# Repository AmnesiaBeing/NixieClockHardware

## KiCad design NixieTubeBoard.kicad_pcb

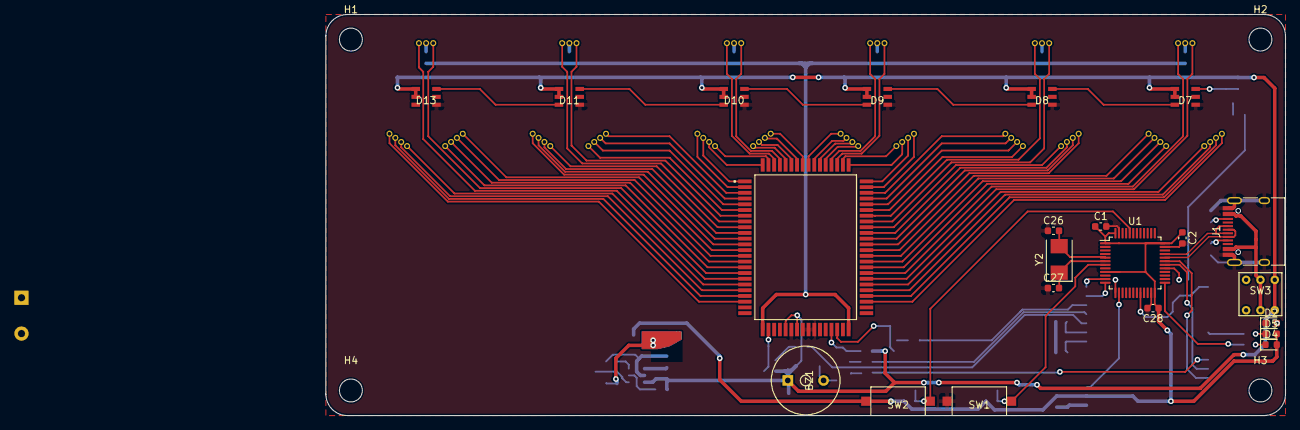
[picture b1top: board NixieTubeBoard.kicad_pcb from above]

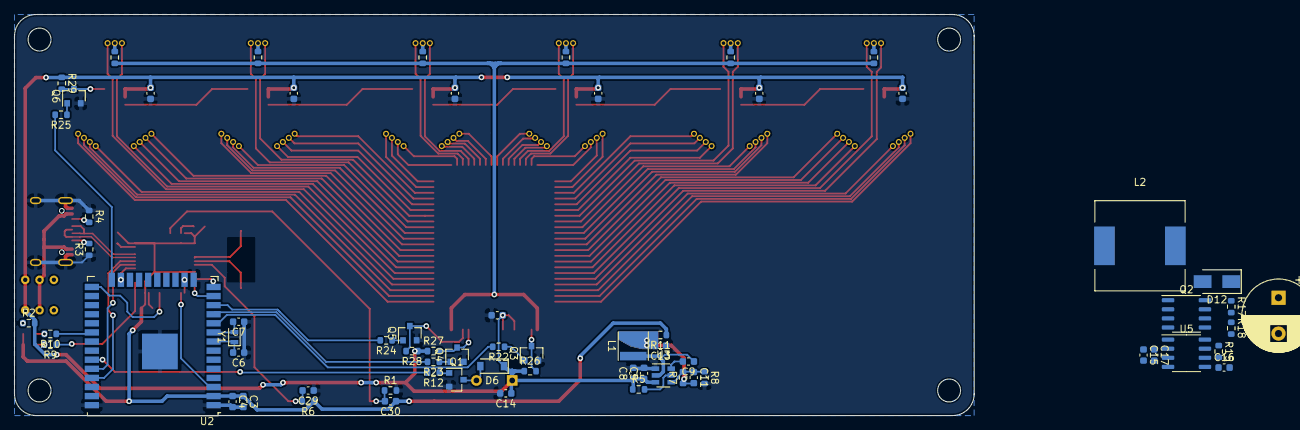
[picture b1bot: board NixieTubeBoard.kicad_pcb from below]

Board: 2 copper layers, 134.0 x 56.0 mm, 98 parts (66 on the bottom side), 124 nets.

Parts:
BZ1: Buzzer_C200213
C1, C3, C28: 100uF; C_0603_1608Metric
C2, C4, C8, C9, C16, C25: 100nF; C_0603_1608Metric
C5, C13: 22uF; C_0603_1608Metric
C6, C7, C14, C19, C20, C21, C22, C23, C26, C27, C29, C30: C; C_0603_1608Metric
C11: NC; C_0603_1608Metric
C15: 470uF; C_0603_1608Metric
C17: 330uF; C_0603_1608Metric
C18: 10uF/250V; CP_Radial_D10.0mm_P5.00mm
C24: 100nF×6; C_0603_1608Metric
D2: RED; LED_0603_1608Metric
D4: GREEN; LED_0603_1608Metric
D5: BLUE; LED_0603_1608Metric
D6: 1N4148; D_SOD-123
D7, D8, D9, D10, D11, D13: TC3838
D12: ES1J; D_SMA
H1, H2, H3, H4: MountingHole; MountingHole_3.2mm_M3
J1: USB_C_Receptacle_USB2.0; USB_C_Receptacle_HRO_TYPE-C-31-M-12
L1: 2.2uH; L_Taiyo-Yuden_MD-4040
L2: 220uH; L_12x12mm_H4.5mm
N1, N2, N3, N4, N5: NixieTube; NixieTubeJack
N6: NixieTube×6; NixieTubeJack
Q1, Q3, Q4, Q5, Q6: S8050_BEC; SOT-23
Q2: FDS2672CT; SO-8_3.9x4.9mm_P1.27mm
R1, R6, R8, R26, R27, R28, R29: 10KΩ; R_0603_1608Metric
R2, R9, R10: 1KΩ; R_0603_1608Metric
R3, R4: 5.1KΩ; R_0603_1608Metric
R5: 100KΩ; R_0603_1608Metric
R7: 30KΩ; R_0603_1608Metric
R11: 0; R_0603_1608Metric
R12, R22, R23, R24, R25: R; R_0603_1608Metric
R13, R14, R16, R19, R20, R21: 33KΩ; R_0603_1608Metric
R15: 50mΩ; R_0603_1608Metric
R17: 1.8MΩ; R_0603_1608Metric
R18: 16KΩ; R_0603_1608Metric
SW1, SW2: SW_Push; BUTTON_C2681479
SW3: SW_DPDT_x2; BUTTON_C2681587
U1: STM32L433CBTx; LQFP-48_7x7mm_P0.5mm
U2: ESP32-WROOM-32U
U3: TPS564201; SOT-23-6
U5: MAX1771ESA; SO-8_3.9x4.9mm_P1.27mm
U6: HV507PG-G; QFP80P2390X1790X340-80N
Y1: 32.738kHz; Crystal_SMD_2012-2Pin_2.0x1.2mm
Y2: 32.738kHz; Crystal_SMD_5032-2Pin_5.0x3.2mm

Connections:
+3V3: C1.1, C2.1, C3.1, C4.1, C28.1, C30.1, D4.2, D5.2, R6.1, R11.1, SW2.1, U1.1, U1.9, U1.24, U1.36, U1.48, U2.2
+5V: BZ1.1, C5.1, C8.1, C14.1, C15.1, C17.1, C19.1, C20.1, C21.1, C22.1, C23.1, C24.1, C25.2, D6.1, D7.4, D7.5, D8.4, D8.5, D9.4, D9.5, D10.4, D10.5, D11.4, D11.5, D13.4, D13.5, L2.1, R2.2, R5.1, R26.1, R27.1, R28.1, R29.1, SW3.3, SW3.6, U3.3, U5.2, U6.29, U6.31
/32K_XN: C7.2, U2.9, Y1.2
/32K_XP: C6.2, U2.8, Y1.1
/BUZZER: R12.2, U2.33
/DOWNLOADING: R9.1, U1.25
/ESP32_EN: U1.14, U2.3
/ESP32_IO0: U1.20, U2.25
/ESP32_IO2: R25.2, U2.24
/ESP32_IO12: U1.11, U2.14
/ESP32_IO13: U1.13, U2.16
/ESP32_IO14: U1.12, U2.13
/ESP32_IO15: U1.29, U2.23
/ESP32_IO18: R10.1, U2.30
/ESP32_IO25: R22.2, U2.10
/ESP32_IO26: R23.2, U2.11
/ESP32_IO27: R24.2, U2.12
/ESP32_RXD0: U1.30, U2.34
/ESP32_TXD0: U1.31, U2.35
/HV_CLK_5V: Q4.3, R27.2, U6.37
/HV_DIN_5V: Q3.3, R26.2, U6.26
/HV_LE_5V: Q5.3, R28.2, U6.38
/N10: N1.12, U6.17
/N11: N1.3, U6.18
/N12: N1.4, U6.22
/N13: N1.5, U6.21
/N14: N1.6, U6.20
/N15: N1.7, U6.19
/N16: N1.8, U6.16
/N17: N1.9, U6.15
/N18: N1.10, U6.14
/N19: N1.11, U6.13
/N20: N2.12, U6.7
/N21: N2.3, U6.8
/N22: N2.4, U6.12
/N23: N2.5, U6.11
/N24: N2.6, U6.10
/N25: N2.7, U6.9
/N26: N2.8, U6.6
/N27: N2.9, U6.5
/N28: N2.10, U6.4
/N29: N2.11, U6.3
/N30: N3.12, U6.77
/N31: N3.3, U6.78
/N32: N3.4, U6.2
/N33: N3.5, U6.1
/N34: N3.6, U6.80
/N35: N3.7, U6.79
/N36: N3.8, U6.76
/N37: N3.9, U6.75
/N38: N3.10, U6.74
/N39: N3.11, U6.73
/N40: N4.12, U6.67
/N41: N4.3, U6.68
/N42: N4.4, U6.72
/N43: N4.5, U6.71
/N44: N4.6, U6.70
/N45: N4.7, U6.69
/N46: N4.8, U6.66
/N47: N4.9, U6.65
/N48: N4.10, U6.64
/N49: N4.11, U6.63
/N50: N5.12, U6.57
/N51: N5.3, U6.58
/N52: N5.4, U6.62
/N53: N5.5, U6.61
/N54: N5.6, U6.60
/N55: N5.7, U6.59
/N56: N5.8, U6.56
/N57: N5.9, U6.55
/N58: N5.10, U6.54
/N59: N5.11, U6.53
/N60: N6.12, U6.47
/N61: N6.3, U6.48
/N62: N6.4, U6.52
/N63: N6.5, U6.51
/N64: N6.6, U6.50
/N65: N6.7, U6.49
/N66: N6.8, U6.46
/N67: N6.9, U6.45
/N68: N6.10, U6.44
/N69: N6.11, U6.43
/RGBLED_5V: D7.3, Q6.3, R29.2
/STM32_BOOT0: C30.2, R1.1, SW2.2, U1.44
/STM32_RST: C29.2, R6.2, SW1.2, U1.7
/USB_D+: J1.A6, J1.B6, U1.33
/USB_D-: J1.A7, J1.B7, U1.32
GND: C1.2, C2.2, C3.2, C4.2, C5.2, C6.1, C7.1, C8.2, C13.1, C14.2, C15.2, C16.2, C17.2, C18.2, C19.2, C20.2, C21.2, C22.2, C23.2, C24.2, C25.1, C26.1, C27.1, C28.2, C29.1, D2.1, D7.1, D8.1, D9.1, D10.1, D11.1, D13.1, J1.A1, J1.A12, J1.B1, J1.B12, J1.S1, Q1.2, Q3.2, Q4.2, Q5.2, Q6.2, R1.2, R3.1, R4.1, R8.2, R15.2, R18.2, SW1.1, U1.8, U1.23, U1.35, U1.47, U2.1, U2.15, U2.38, U2.39, U3.1, U5.6, U5.7, U6.30, U6.32, U6.33, U6.34
unnamed: BZ1.2, D6.2, Q1.3
unnamed: C9.1, L1.1, U3.2
unnamed: C9.2, U3.6
unnamed: C11.1, R7.2, R8.1, U3.4
unnamed: C11.2, C13.2, L1.2, R7.1, R11.2
unnamed: C16.1, U5.5
unnamed: C26.2, U1.5, Y2.2
unnamed: C27.2, U1.6, Y2.1
unnamed: D2.2, R2.1
unnamed: D4.1, R9.2
unnamed: D5.1, R10.2
unnamed: D7.6, D8.3
unnamed: D8.6, D9.3
unnamed: D9.6, D10.3
unnamed: D10.6, D11.3
unnamed: D11.6, D13.3
unnamed: D12.2, L2.2, Q2.5, Q2.6, Q2.7, Q2.8
unnamed: J1.A4, J1.A9, J1.B4, J1.B9, SW3.2, SW3.5
unnamed: J1.A5, R3.2
unnamed: J1.B5, R4.2
unnamed: N1.1, R13.2
unnamed: N2.1, R14.2
unnamed: N3.1, R16.2
unnamed: N4.1, R19.2
unnamed: N5.1, R20.2
unnamed: N6.1, R21.2
unnamed: Q1.1, R12.1
unnamed: Q2.1, Q2.2, Q2.3, R15.1, U5.8
unnamed: Q2.4, U5.1
unnamed: Q3.1, R22.1
unnamed: Q4.1, R23.1
unnamed: Q5.1, R24.1
unnamed: Q6.1, R25.1
unnamed: R5.2, U3.5
unnamed: R17.2, R18.1, U5.3
VPP: C18.1, D12.1, R13.1, R14.1, R16.1, R17.1, R19.1, R20.1, R21.1, U6.25, U6.40

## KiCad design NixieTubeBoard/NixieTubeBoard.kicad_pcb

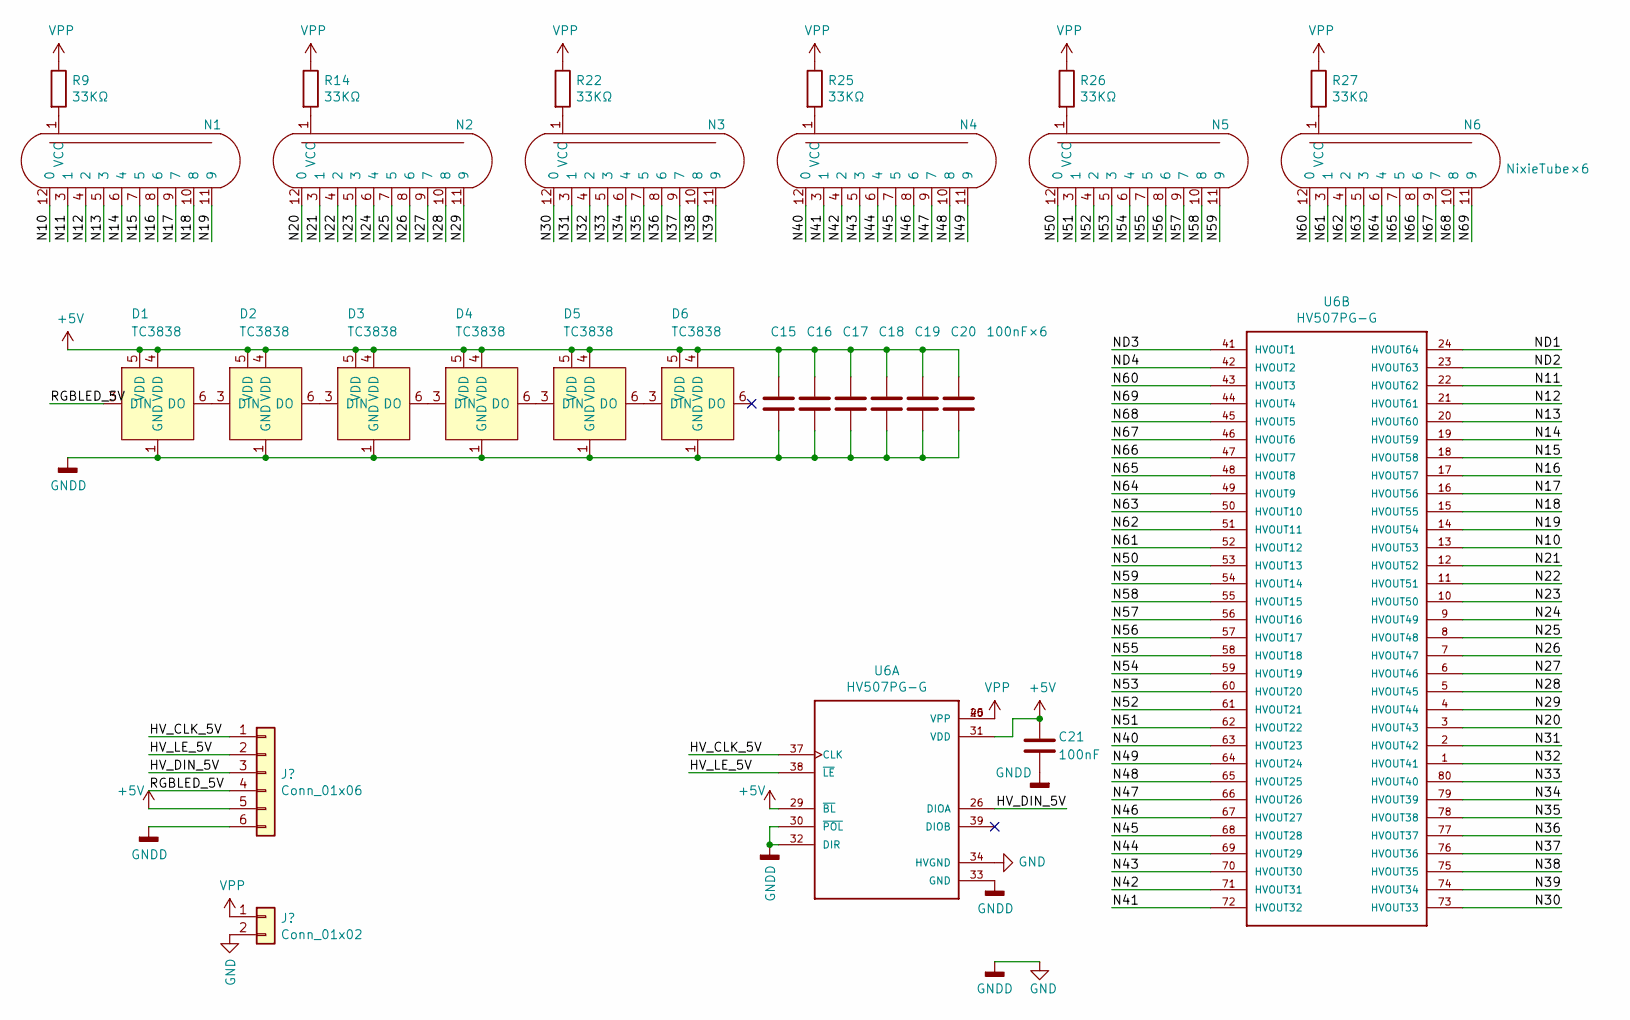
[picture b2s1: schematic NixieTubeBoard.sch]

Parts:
C15, C16, C17, C18, C19: C; C_0603_1608Metric
C20: 100nF×6; C_0603_1608Metric
C21: 100nF; C_0603_1608Metric
D1, D2, D3, D4, D5, D6: TC3838
N1, N2, N3, N4, N5: NixieTube; NixieTubeJack
N6: NixieTube×6; NixieTubeJack
R9, R14, R22, R25, R26, R27: 33KΩ; R_0603_1608Metric
U6: HV507PG-G; QFP80P2390X1790X340-80N

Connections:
+5V: C15.1, C16.1, C17.1, C18.1, C19.1, C20.1, C21.2, D1.4 (VDD), D1.5 (VDD), D2.4 (VDD), D2.5 (VDD), D3.4 (VDD), D3.5 (VDD), D4.4 (VDD), D4.5 (VDD), D5.4 (VDD), D5.5 (VDD), D6.4 (VDD), D6.5 (VDD), U6.29 (~BL~), U6.31 (VDD)
/HV_CLK_5V: U6.37 (CLK)
/HV_DIN_5V: U6.26 (DIOA)
/HV_LE_5V: U6.38 (~LE~)
/N10: N1.12 (0), U6.13 (HVOUT53)
/N11: N1.3 (1), U6.22 (HVOUT62)
/N12: N1.4 (2), U6.21 (HVOUT61)
/N13: N1.5 (3), U6.20 (HVOUT60)
/N14: N1.6 (4), U6.19 (HVOUT59)
/N15: N1.7 (5), U6.18 (HVOUT58)
/N16: N1.8 (6), U6.17 (HVOUT57)
/N17: N1.9 (7), U6.16 (HVOUT56)
/N18: N1.10 (8), U6.15 (HVOUT55)
/N19: N1.11 (9), U6.14 (HVOUT54)
/N20: N2.12 (0), U6.3 (HVOUT43)
/N21: N2.3 (1), U6.12 (HVOUT52)
/N22: N2.4 (2), U6.11 (HVOUT51)
/N23: N2.5 (3), U6.10 (HVOUT50)
/N24: N2.6 (4), U6.9 (HVOUT49)
/N25: N2.7 (5), U6.8 (HVOUT48)
/N26: N2.8 (6), U6.7 (HVOUT47)
/N27: N2.9 (7), U6.6 (HVOUT46)
/N28: N2.10 (8), U6.5 (HVOUT45)
/N29: N2.11 (9), U6.4 (HVOUT44)
/N30: N3.12 (0), U6.73 (HVOUT33)
/N31: N3.3 (1), U6.2 (HVOUT42)
/N32: N3.4 (2), U6.1 (HVOUT41)
/N33: N3.5 (3), U6.80 (HVOUT40)
/N34: N3.6 (4), U6.79 (HVOUT39)
/N35: N3.7 (5), U6.78 (HVOUT38)
/N36: N3.8 (6), U6.77 (HVOUT37)
/N37: N3.9 (7), U6.76 (HVOUT36)
/N38: N3.10 (8), U6.75 (HVOUT35)
/N39: N3.11 (9), U6.74 (HVOUT34)
/N40: N4.12 (0), U6.63 (HVOUT23)
/N41: N4.3 (1), U6.72 (HVOUT32)
/N42: N4.4 (2), U6.71 (HVOUT31)
/N43: N4.5 (3), U6.70 (HVOUT30)
/N44: N4.6 (4), U6.69 (HVOUT29)
/N45: N4.7 (5), U6.68 (HVOUT28)
/N46: N4.8 (6), U6.67 (HVOUT27)
/N47: N4.9 (7), U6.66 (HVOUT26)
/N48: N4.10 (8), U6.65 (HVOUT25)
/N49: N4.11 (9), U6.64 (HVOUT24)
/N50: N5.12 (0), U6.53 (HVOUT13)
/N51: N5.3 (1), U6.62 (HVOUT22)
/N52: N5.4 (2), U6.61 (HVOUT21)
/N53: N5.5 (3), U6.60 (HVOUT20)
/N54: N5.6 (4), U6.59 (HVOUT19)
/N55: N5.7 (5), U6.58 (HVOUT18)
/N56: N5.8 (6), U6.57 (HVOUT17)
/N57: N5.9 (7), U6.56 (HVOUT16)
/N58: N5.10 (8), U6.55 (HVOUT15)
/N59: N5.11 (9), U6.54 (HVOUT14)
/N60: N6.12 (0), U6.43 (HVOUT3)
/N61: N6.3 (1), U6.52 (HVOUT12)
/N62: N6.4 (2), U6.51 (HVOUT11)
/N63: N6.5 (3), U6.50 (HVOUT10)
/N64: N6.6 (4), U6.49 (HVOUT9)
/N65: N6.7 (5), U6.48 (HVOUT8)
/N66: N6.8 (6), U6.47 (HVOUT7)
/N67: N6.9 (7), U6.46 (HVOUT6)
/N68: N6.10 (8), U6.45 (HVOUT5)
/N69: N6.11 (9), U6.44 (HVOUT4)
/RGBLED_5V: D1.3 (DIN)
GND: C15.2, C16.2, C17.2, C18.2, C19.2, C20.2, C21.1, D1.1 (GND), D2.1 (GND), D3.1 (GND), D4.1 (GND), D5.1 (GND), D6.1 (GND), U6.30 (~POL~), U6.32 (DIR), U6.33 (GND), U6.34 (HVGND)
unnamed: D1.6 (DO), D2.3 (DIN)
unnamed: D2.6 (DO), D3.3 (DIN)
unnamed: D3.6 (DO), D4.3 (DIN)
unnamed: D4.6 (DO), D5.3 (DIN)
unnamed: D5.6 (DO), D6.3 (DIN)
unnamed: N1.1 (VCC), R9.2
unnamed: N2.1 (VCC), R14.2
unnamed: N3.1 (VCC), R22.2
unnamed: N4.1 (VCC), R25.2
unnamed: N5.1 (VCC), R26.2
unnamed: N6.1 (VCC), R27.2
VPP: R9.1, R14.1, R22.1, R25.1, R26.1, R27.1, U6.25 (VPP), U6.40 (VPP)

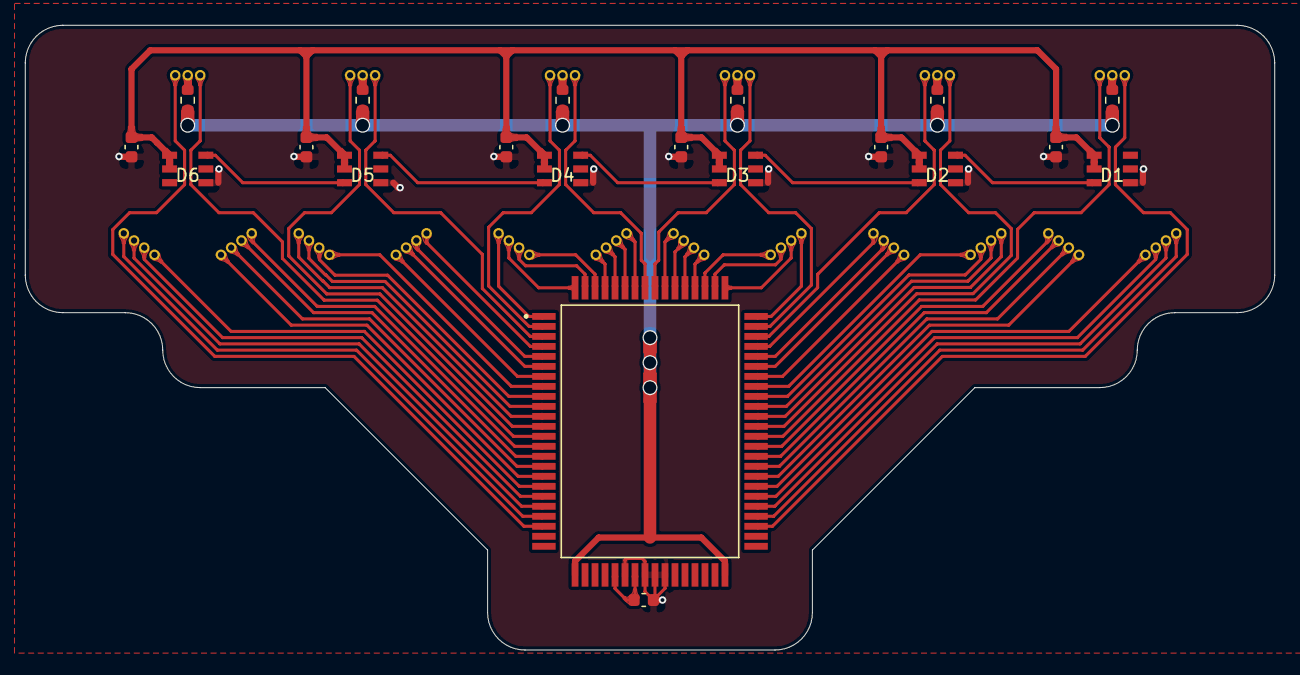
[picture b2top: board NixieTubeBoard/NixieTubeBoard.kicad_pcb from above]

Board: 2 copper layers, 100.0 x 50.0 mm, 26 parts (0 on the bottom side), 74 nets.

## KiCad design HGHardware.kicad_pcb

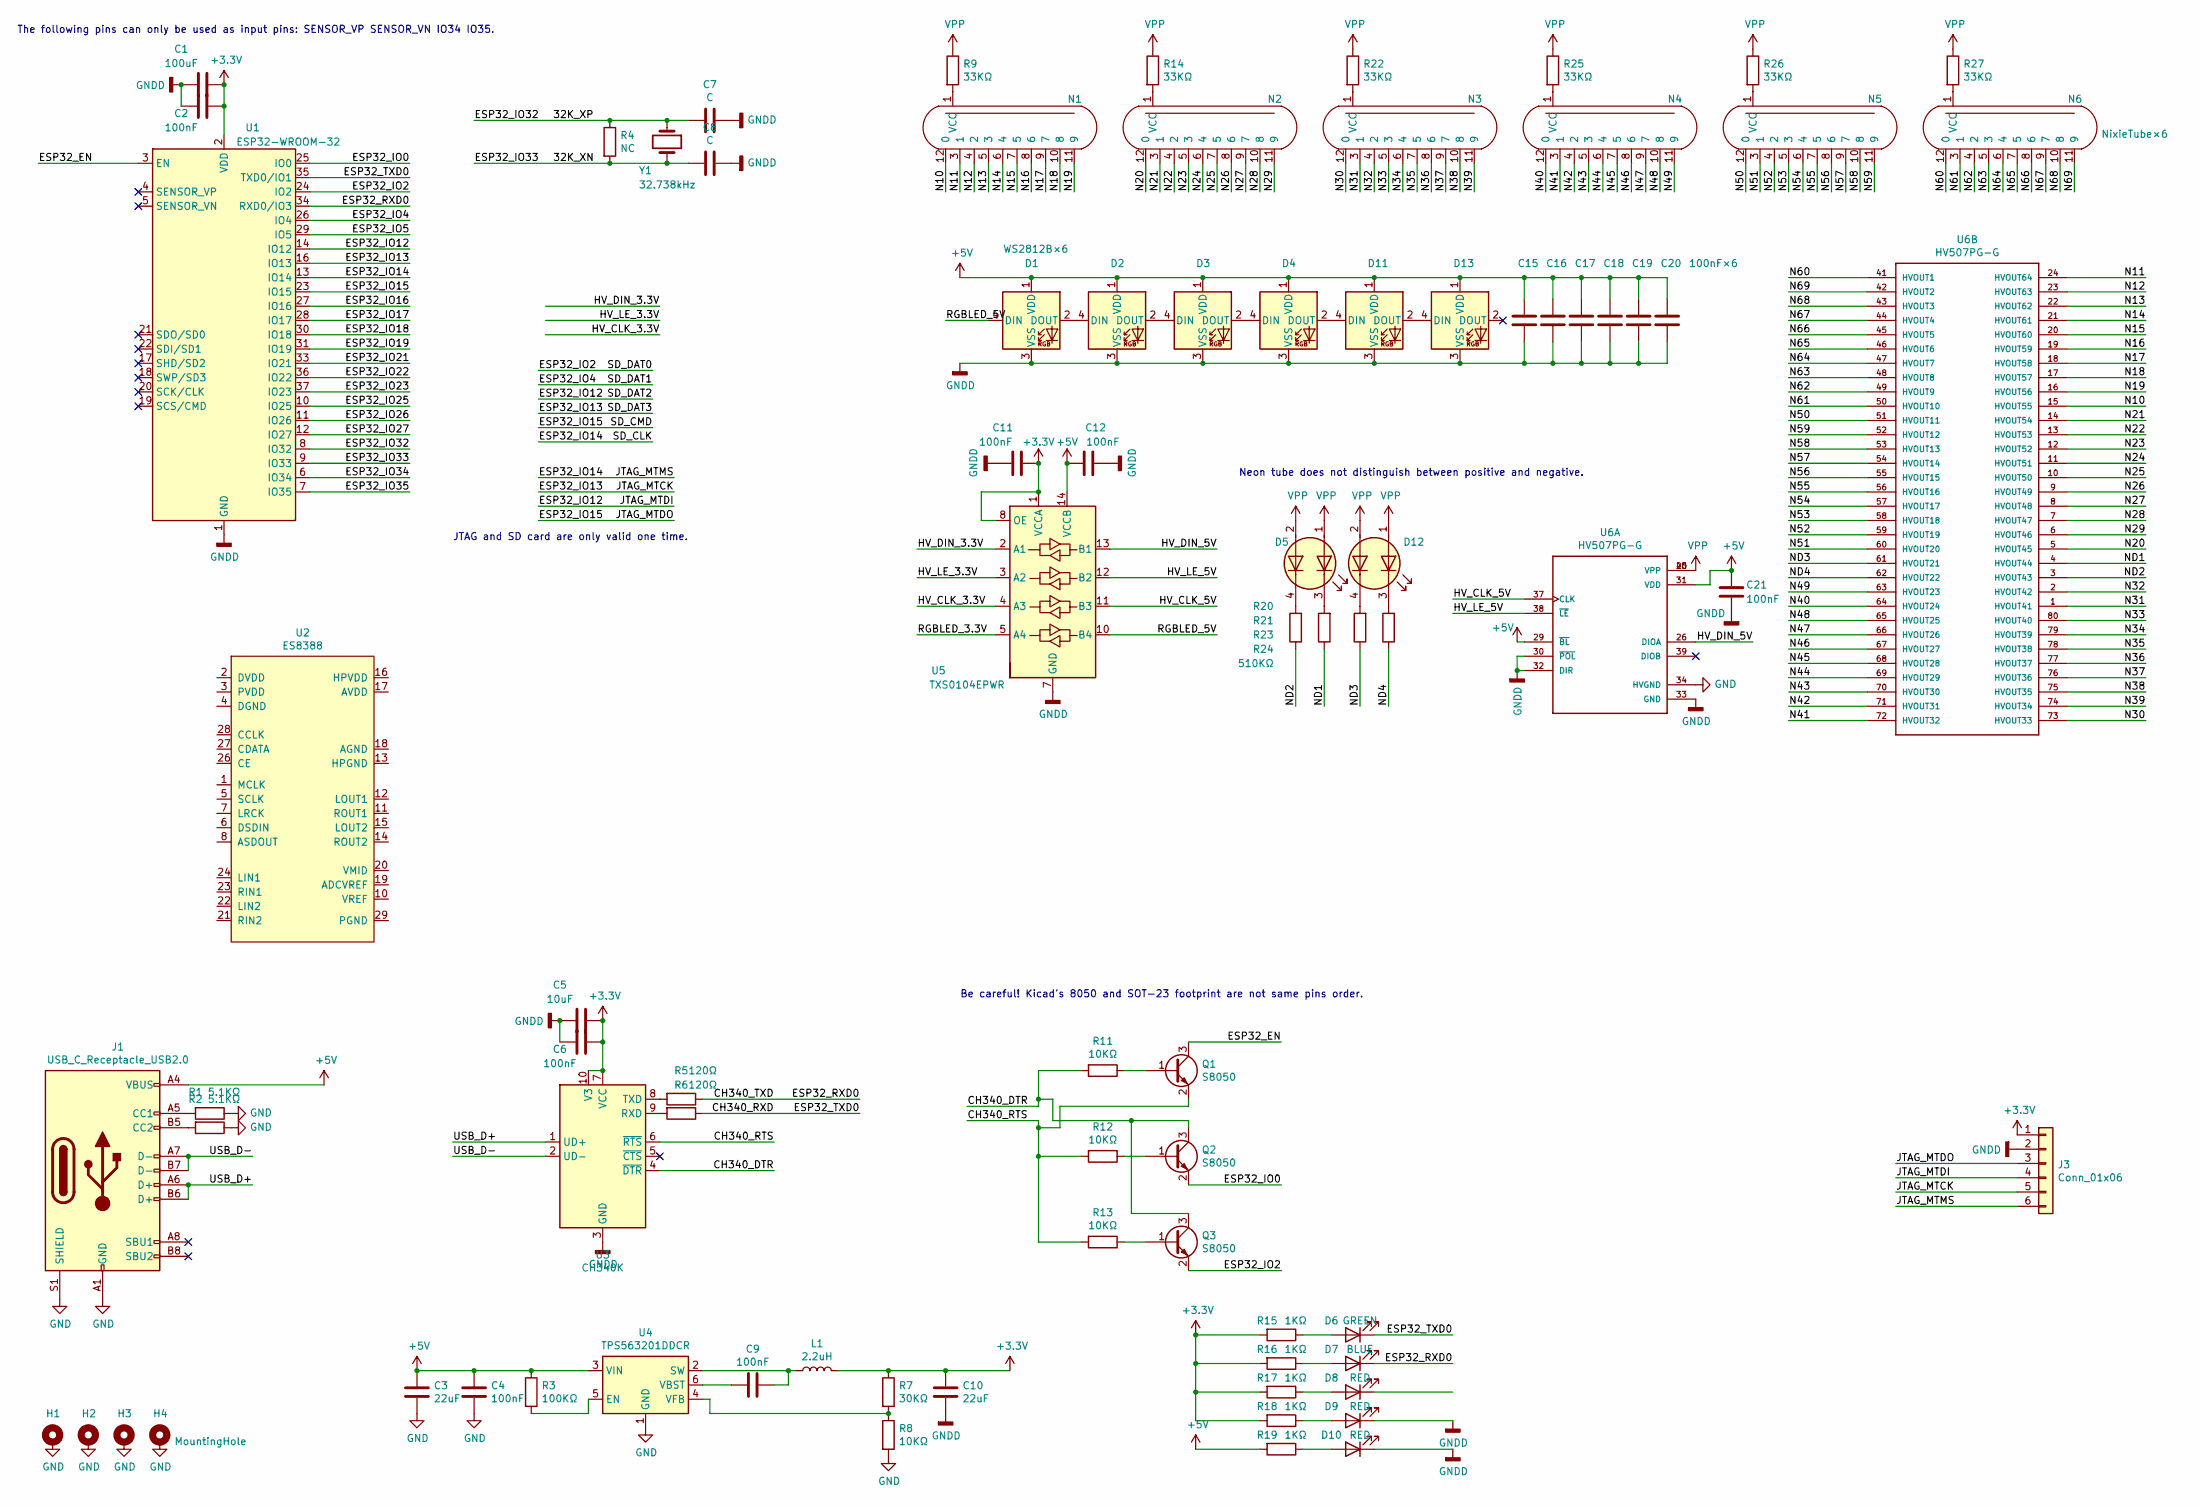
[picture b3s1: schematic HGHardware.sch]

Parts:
C1: 100uF; C_0603_1608Metric
C2, C4, C6, C9, C11, C12, C21: 100nF; C_0603_1608Metric
C3, C10: 22uF; C_0603_1608Metric
C5: 10uF; C_0603_1608Metric
C7, C8, C15, C16, C17, C18, C19: C; C_0603_1608Metric
C20: 100nF×6; C_0603_1608Metric
D1: WS2812B×6; LED_WS2812B_PLCC4_5.0x5.0mm_P3.2mm
D2, D3: WS2812B-2020; LED_WS2812B_PLCC4_5.0x5.0mm_P3.2mm
D4, D11, D13: WS2812C; LED_WS2812B_PLCC4_5.0x5.0mm_P3.2mm
D5, D12: LED_Dual_AACC; PinSocket_2x02_P2.00mm_Vertical
D6: GREEN; LED_0603_1608Metric
D7: BLUE; LED_0603_1608Metric
D8, D9, D10: RED; LED_0603_1608Metric
H1, H2, H3, H4: MountingHole; MountingHole_3.2mm_M3
J1: USB_C_Receptacle_USB2.0; USB_C_Receptacle_HRO_TYPE-C-31-M-12
J3: Conn_01x06; PinHeader_1x06_P2.54mm_Vertical
L1: 2.2uH; L_Taiyo-Yuden_MD-4040
N1, N2, N3, N4, N5: NixieTube; NixieTubeJack
N6: NixieTube×6; NixieTubeJack
Q1, Q2, Q3: S8050; SOT-23
R1, R2: 5.1KΩ; R_0603_1608Metric
R3: 100KΩ; R_0603_1608Metric
R4: NC; R_0603_1608Metric
R5, R6: 120Ω; R_0603_1608Metric
R7: 30KΩ; R_0603_1608Metric
R8, R11, R12, R13: 10KΩ; R_0603_1608Metric
R9, R14, R22, R25, R26, R27: 33KΩ; R_0603_1608Metric
R15, R16, R17, R18, R19: 1KΩ; R_0603_1608Metric
R20: 510KΩ; R_0603_1608Metric
R21, R23, R24: 510KO; R_0603_1608Metric
U1: ESP32-WROOM-32
U2: ES8388; QFN-28-1EP_4x4mm_P0.4mm_EP2.4x2.4mm_ThermalVias
U3: CH340K; SSOP-10_3.9x4.9mm_P1.00mm
U4: TPS563201DDCR; SOT-23-6
U5: TXS0104EPWR; TSSOP-14_4.4x5mm_P0.65mm
U6: HV507PG-G; QFP80P2390X1790X340-80N
Y1: 32.738kHz; Crystal_SMD_2012-2Pin_2.0x1.2mm

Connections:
+3V3: C1.1, C2.1, C5.1, C6.1, C10.2, C11.1, J3.1, L1.2, R7.1, R15.2, R16.2, R17.2, R18.2, U1.2 (VDD), U3.7 (VCC), U3.10 (V3), U5.1 (VCCA), U5.8 (OE); also elsewhere on the board
+5V: C3.1, C4.1, C12.1, C15.1, C16.1, C17.1, C18.1, C19.1, C20.1, C21.2, D1.1 (VDD), D2.1 (VDD), D3.1 (VDD), D4.1 (VDD), D11.1 (VDD), D13.1 (VDD), J1.A4 (VBUS), J1.A9 (VBUS), J1.B4 (VBUS), J1.B9 (VBUS), R3.1, R19.2, U4.3 (VIN), U5.14 (VCCB), U6.29 (~BL~), U6.31 (VDD)
/32K_XN: C8.2, R4.2, U1.9 (IO33), Y1.2
/32K_XP: C7.2, R4.1, U1.8 (IO32), Y1.1
/CH340_DTR: Q2.3 (C), Q3.3 (C), R11.2, U3.4 (~DTR)
/CH340_RTS: Q1.2 (E), R12.2, R13.2, U3.6 (~RTS)
/CH340_RXD: D6.1 (K), R6.1, U1.35 (TXD0/IO1)
/CH340_TXD: D7.1 (K), R5.1, U1.34 (RXD0/IO3)
/ESP32_EN: Q1.3 (C), U1.3 (EN)
/ESP32_IO0: Q2.2 (E), U1.25 (IO0)
/ESP32_IO2: Q3.2 (E), U1.24 (IO2)
/ESP32_IO4: U1.26 (IO4)
/ESP32_IO5: U1.29 (IO5)
/ESP32_IO12: J3.4, U1.14 (IO12)
/ESP32_IO13: J3.5, U1.16 (IO13)
/ESP32_IO14: J3.6, U1.13 (IO14)
/ESP32_IO15: J3.3, U1.23 (IO15)
/ESP32_IO16: U1.27 (IO16)
/ESP32_IO17: U1.28 (IO17)
/ESP32_IO18: U1.30 (IO18)
/ESP32_IO19: U1.31 (IO19)
/ESP32_IO21: U1.33 (IO21)
/ESP32_IO22: U1.36 (IO22)
/ESP32_IO23: U1.37 (IO23)
/ESP32_IO25: U1.10 (IO25)
/ESP32_IO26: U1.11 (IO26)
/ESP32_IO27: U1.12 (IO27)
/ESP32_IO34: U1.6 (IO34)
/ESP32_IO35: U1.7 (IO35)
/HV_CLK_3.3V: U5.4 (A3)
/HV_CLK_5V: U5.11 (B3), U6.37 (CLK)
/HV_DIN_3.3V: U5.2 (A1)
/HV_DIN_5V: U5.13 (B1), U6.26 (DIOA)
/HV_LE_3.3V: U5.3 (A2)
/HV_LE_5V: U5.12 (B2), U6.38 (~LE~)
/N10: N1.12 (0), U6.15 (HVOUT55)
/N11: N1.3 (1), U6.24 (HVOUT64)
/N12: N1.4 (2), U6.23 (HVOUT63)
/N13: N1.5 (3), U6.22 (HVOUT62)
/N14: N1.6 (4), U6.21 (HVOUT61)
/N15: N1.7 (5), U6.20 (HVOUT60)
/N16: N1.8 (6), U6.19 (HVOUT59)
/N17: N1.9 (7), U6.18 (HVOUT58)
/N18: N1.10 (8), U6.17 (HVOUT57)
/N19: N1.11 (9), U6.16 (HVOUT56)
/N20: N2.12 (0), U6.5 (HVOUT45)
/N21: N2.3 (1), U6.14 (HVOUT54)
/N22: N2.4 (2), U6.13 (HVOUT53)
/N23: N2.5 (3), U6.12 (HVOUT52)
/N24: N2.6 (4), U6.11 (HVOUT51)
/N25: N2.7 (5), U6.10 (HVOUT50)
/N26: N2.8 (6), U6.9 (HVOUT49)
/N27: N2.9 (7), U6.8 (HVOUT48)
/N28: N2.10 (8), U6.7 (HVOUT47)
/N29: N2.11 (9), U6.6 (HVOUT46)
/N30: N3.12 (0), U6.73 (HVOUT33)
/N31: N3.3 (1), U6.1 (HVOUT41)
/N32: N3.4 (2), U6.2 (HVOUT42)
/N33: N3.5 (3), U6.80 (HVOUT40)
/N34: N3.6 (4), U6.79 (HVOUT39)
/N35: N3.7 (5), U6.78 (HVOUT38)
/N36: N3.8 (6), U6.77 (HVOUT37)
/N37: N3.9 (7), U6.76 (HVOUT36)
/N38: N3.10 (8), U6.75 (HVOUT35)
/N39: N3.11 (9), U6.74 (HVOUT34)
/N40: N4.12 (0), U6.64 (HVOUT24)
/N41: N4.3 (1), U6.72 (HVOUT32)
/N42: N4.4 (2), U6.71 (HVOUT31)
/N43: N4.5 (3), U6.70 (HVOUT30)
/N44: N4.6 (4), U6.69 (HVOUT29)
/N45: N4.7 (5), U6.68 (HVOUT28)
/N46: N4.8 (6), U6.67 (HVOUT27)
/N47: N4.9 (7), U6.66 (HVOUT26)
/N48: N4.10 (8), U6.65 (HVOUT25)
/N49: N4.11 (9), U6.63 (HVOUT23)
/N50: N5.12 (0), U6.51 (HVOUT11)
/N51: N5.3 (1), U6.60 (HVOUT20)
/N52: N5.4 (2), U6.59 (HVOUT19)
/N53: N5.5 (3), U6.58 (HVOUT18)
/N54: N5.6 (4), U6.57 (HVOUT17)
/N55: N5.7 (5), U6.56 (HVOUT16)
/N56: N5.8 (6), U6.55 (HVOUT15)
/N57: N5.9 (7), U6.54 (HVOUT14)
/N58: N5.10 (8), U6.53 (HVOUT13)
/N59: N5.11 (9), U6.52 (HVOUT12)
/N60: N6.12 (0), U6.41 (HVOUT1)
/N61: N6.3 (1), U6.50 (HVOUT10)
/N62: N6.4 (2), U6.49 (HVOUT9)
/N63: N6.5 (3), U6.48 (HVOUT8)
/N64: N6.6 (4), U6.47 (HVOUT7)
/N65: N6.7 (5), U6.46 (HVOUT6)
/N66: N6.8 (6), U6.45 (HVOUT5)
/N67: N6.9 (7), U6.44 (HVOUT4)
/N68: N6.10 (8), U6.43 (HVOUT3)
/N69: N6.11 (9), U6.42 (HVOUT2)
/ND1: R21.1, U6.4 (HVOUT44)
/ND2: R20.1, U6.3 (HVOUT43)
/ND3: R23.1, U6.61 (HVOUT21)
/ND4: R24.1, U6.62 (HVOUT22)
/RGBLED_3.3V: U5.5 (A4)
/RGBLED_5V: D1.4 (DIN), U5.10 (B4)
/USB_D+: J1.A6 (D+), J1.B6 (D+), U3.1 (UD+)
/USB_D-: J1.A7 (D-), J1.B7 (D-), U3.2 (UD-)
GND: C3.2, C4.2, J1.A1 (GND), J1.A12 (GND), J1.B1 (GND), J1.B12 (GND), J1.S1 (SHIELD), R1.1, R2.1, R8.2, U4.1 (GND), U6.34 (HVGND)
GNDD: C1.2, C2.2, C5.2, C6.2, C7.1, C8.1, C10.1, C11.2, C12.2, C15.2, C16.2, C17.2, C18.2, C19.2, C20.2, C21.1, D1.3 (VSS), D2.3 (VSS), D3.3 (VSS), D4.3 (VSS), D9.1 (K), D10.1 (K), D11.3 (VSS), D13.3 (VSS), J3.2, U1.1 (GND), U1.15 (GND), U1.38 (GND), U1.39 (GND), U3.3 (GND), U5.7 (GND), U6.30 (~POL~), U6.32 (DIR), U6.33 (GND); also elsewhere on the board
unnamed: C9.1, L1.1, U4.2 (SW)
unnamed: C9.2, U4.6 (VBST)
unnamed: D1.2 (DOUT), D2.4 (DIN)
unnamed: D2.2 (DOUT), D3.4 (DIN)
unnamed: D3.2 (DOUT), D4.4 (DIN)
unnamed: D5.3 (K1), R21.2
unnamed: D5.4 (K2), R20.2
unnamed: D6.2 (A), R15.1
unnamed: D7.2 (A), R16.1
unnamed: D8.2 (A), R17.1
unnamed: D9.2 (A), R18.1
unnamed: D10.2 (A), R19.1
unnamed: D11.2 (DOUT), D13.4 (DIN)
unnamed: D4.2 (DOUT), D11.4 (DIN)
unnamed: D12.3 (K1), R24.2
unnamed: D12.4 (K2), R23.2
unnamed: J1.A5 (CC1), R1.2
unnamed: J1.B5 (CC2), R2.2
unnamed: N1.1 (VCC), R9.2
unnamed: N2.1 (VCC), R14.2
unnamed: N3.1 (VCC), R22.2
unnamed: N4.1 (VCC), R25.2
unnamed: N5.1 (VCC), R26.2
unnamed: N6.1 (VCC), R27.2
unnamed: Q1.1 (B), R11.1
unnamed: Q2.1 (B), R12.1
unnamed: Q3.1 (B), R13.1
unnamed: R3.2, U4.5 (EN)
unnamed: R5.2, U3.8 (TXD)
unnamed: R6.2, U3.9 (RXD)
unnamed: R7.2, R8.1, U4.4 (VFB)
VPP: D5.1 (A1), D5.2 (A2), D12.1 (A1), D12.2 (A2), R9.1, R14.1, R22.1, R25.1, R26.1, R27.1, U6.25 (VPP), U6.40 (VPP)

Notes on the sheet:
Neon tube does not distinguish between positive and negative.
The following pins can only be used as input pins: SENSOR_VP SENSOR_VN IO34 IO35.
JTAG and SD card are only valid one time.
Be careful! Kicad's 8050 and SOT-23 footprint are not same pins order.

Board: 2 copper layers, 83 parts (0 on the bottom side), 119 nets, no tracks yet.

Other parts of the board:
C13: 10uF; C_0603_1608Metric
C14: 100nF; C_0603_1608Metric

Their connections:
+3V3: C13.1, C14.1; also elsewhere on the board
GNDD: C13.2, C14.2; also elsewhere on the board

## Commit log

2021-03-04 初次添加，从旧版本开始
2021-03-04 原理图修改，同步
2021-03-06 20210306完善原理图，升压模块将单独使用
2021-03-07 犹豫不决ing
2021-03-11 拆分得七零八落
2021-07-12 改了一堆东西忘了提交了
